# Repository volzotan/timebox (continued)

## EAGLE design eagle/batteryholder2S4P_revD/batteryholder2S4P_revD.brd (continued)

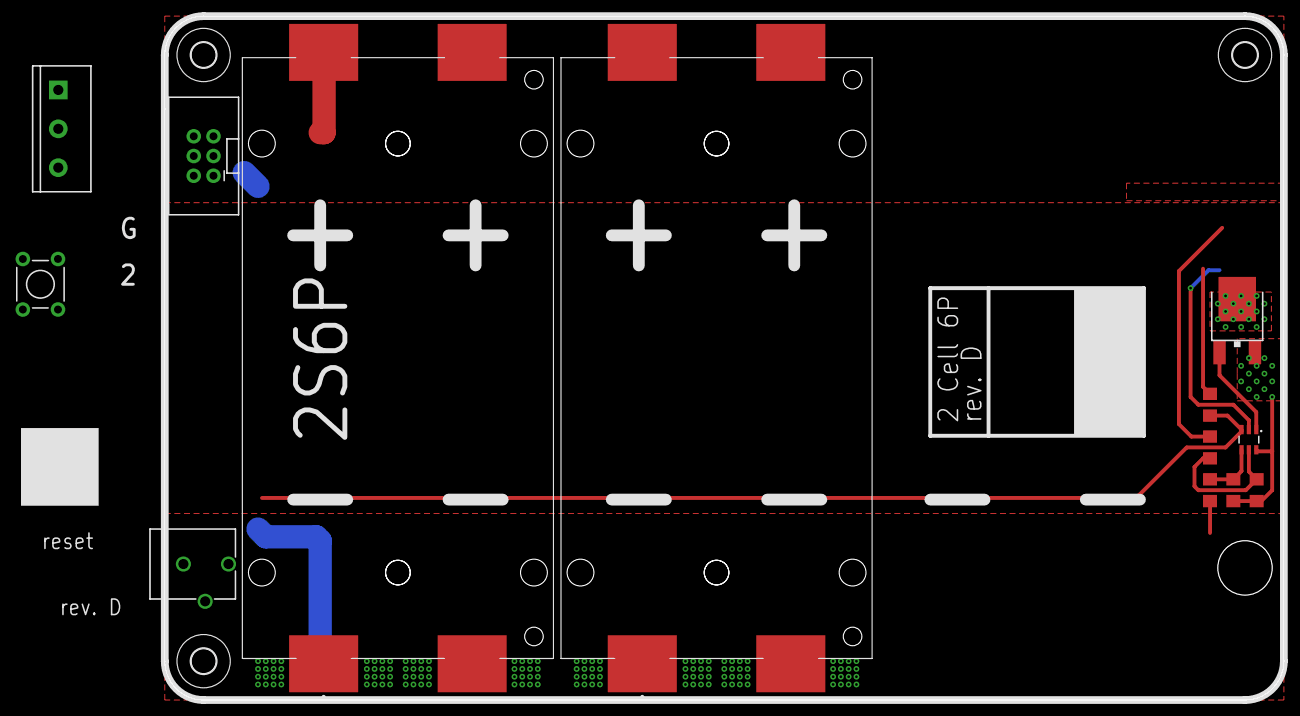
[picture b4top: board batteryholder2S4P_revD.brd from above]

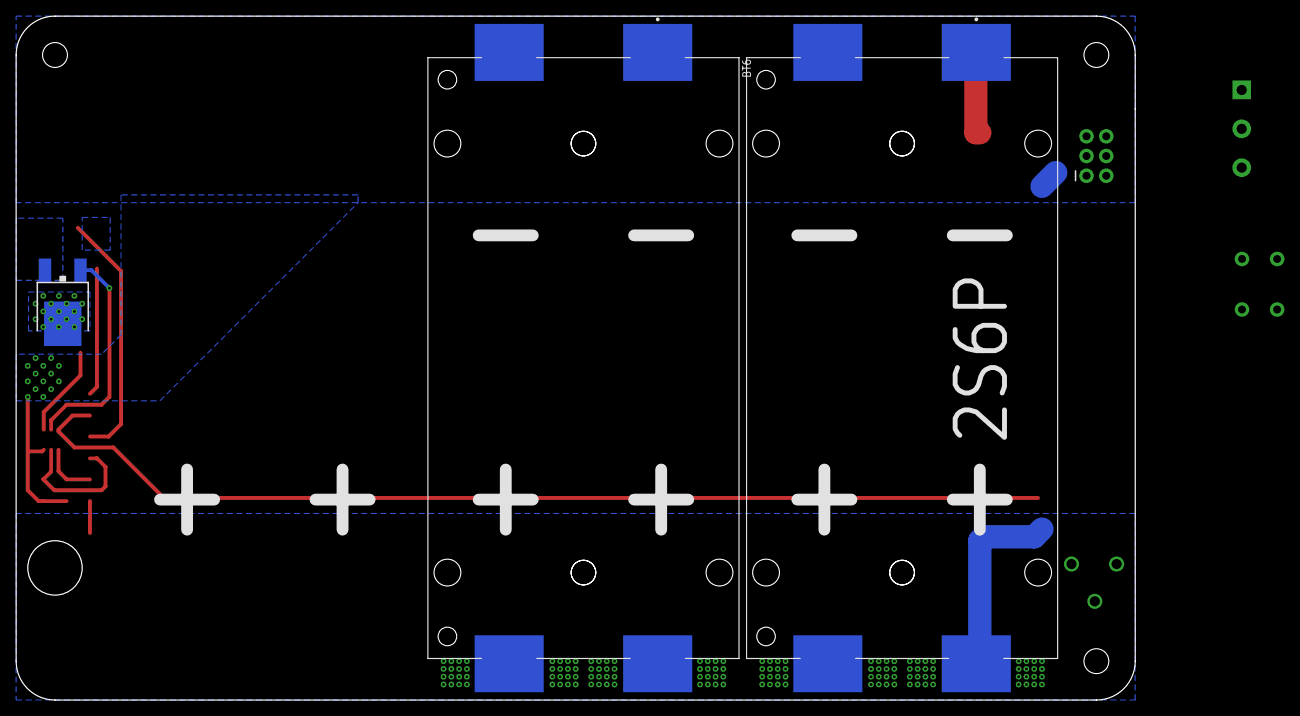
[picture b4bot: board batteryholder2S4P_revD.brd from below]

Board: 2 copper layers, 144.0 x 88.0 mm, 19 parts (3 on the bottom side), 10 nets.

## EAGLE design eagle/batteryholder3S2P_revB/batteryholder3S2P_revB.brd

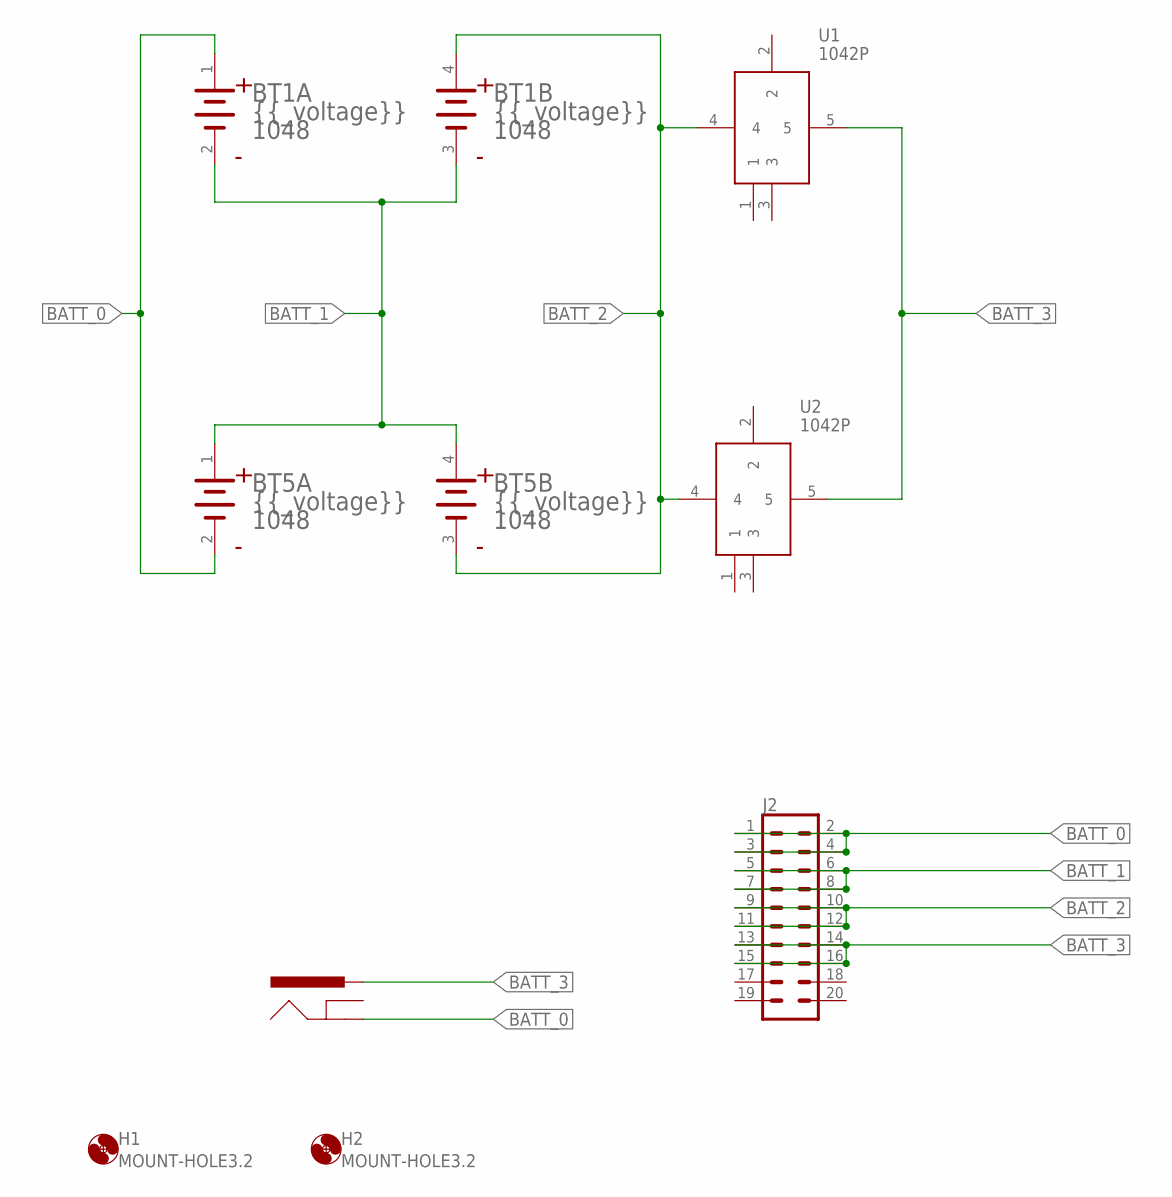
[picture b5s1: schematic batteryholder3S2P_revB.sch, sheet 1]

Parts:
BT1, BT5: KEYSTONE_1048KEYSTONE_1048_0_0; KEYSTONE_1048_0
H1, H2: MOUNT-HOLE3.2; 3,2
J2: CONN_10X2NOSILK; 2X10_NOSILK
J3: POWER_JACKPTH_BREAD; POWER_JACK_PTH_BREAD
U1, U2: 1042P

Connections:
BATT_0: BT1.1 (1_ANODE), BT5.2 (1_CATHODE), J2.1, J2.2, J2.3, J2.4, J3.GND
BATT_1: BT1.2 (1_CATHODE), BT1.3 (2_CATHODE), BT5.1 (1_ANODE), BT5.4 (2_ANODE), J2.5, J2.6, J2.7, J2.8
BATT_2: BT1.4 (2_ANODE), BT5.3 (2_CATHODE), J2.9, J2.10, J2.11, J2.12, U1.4, U2.4
BATT_3: J2.13, J2.14, J2.15, J2.16, J3.PWR, U1.5, U2.5

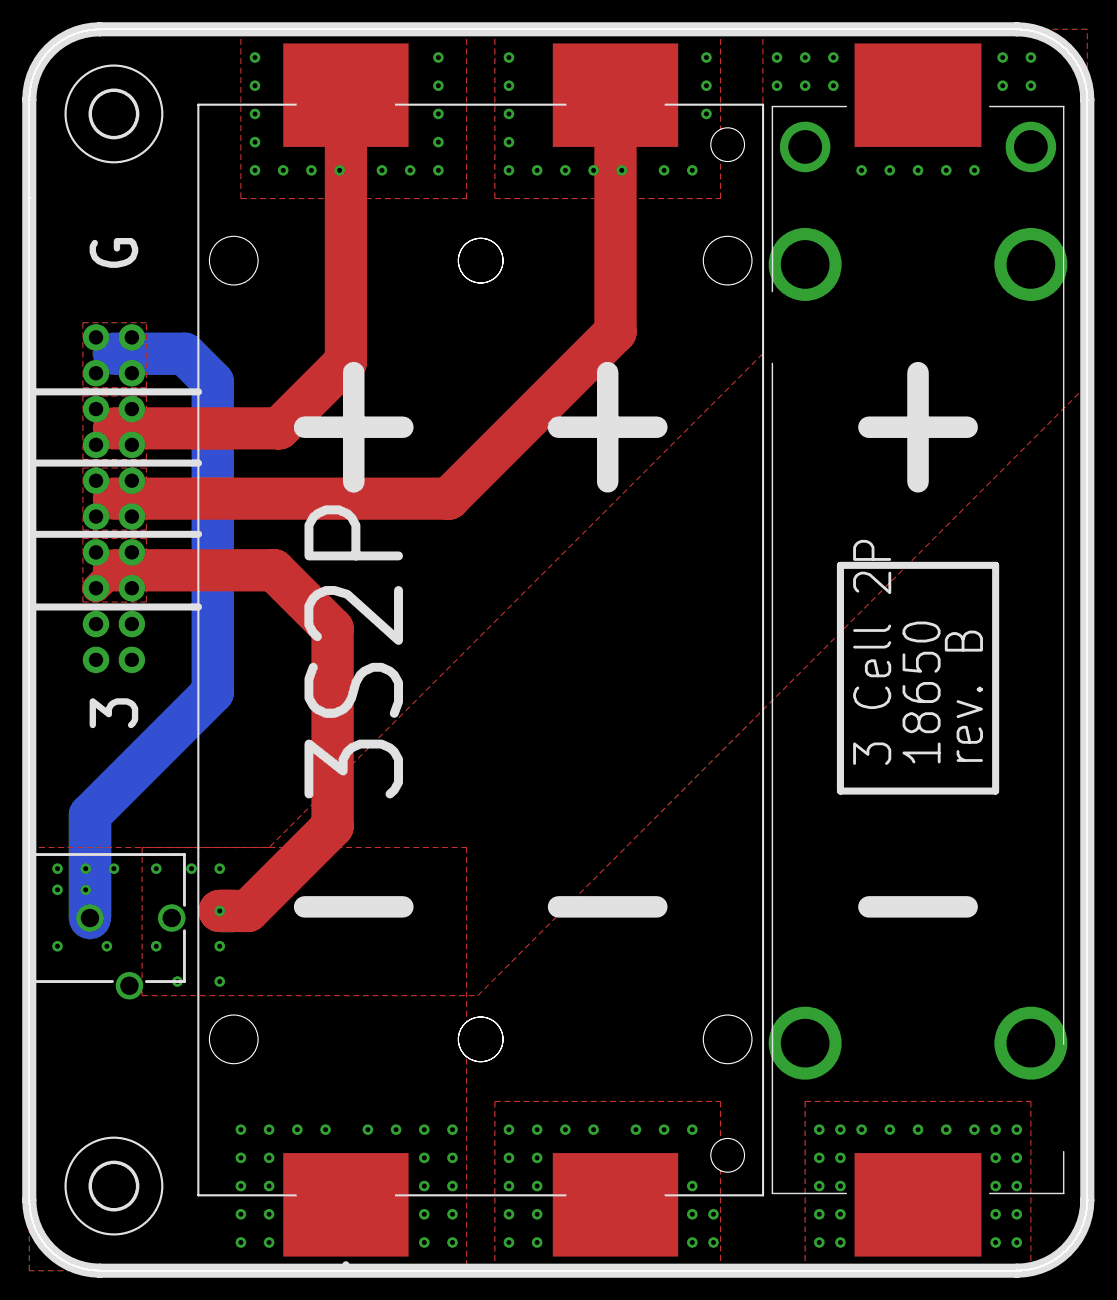
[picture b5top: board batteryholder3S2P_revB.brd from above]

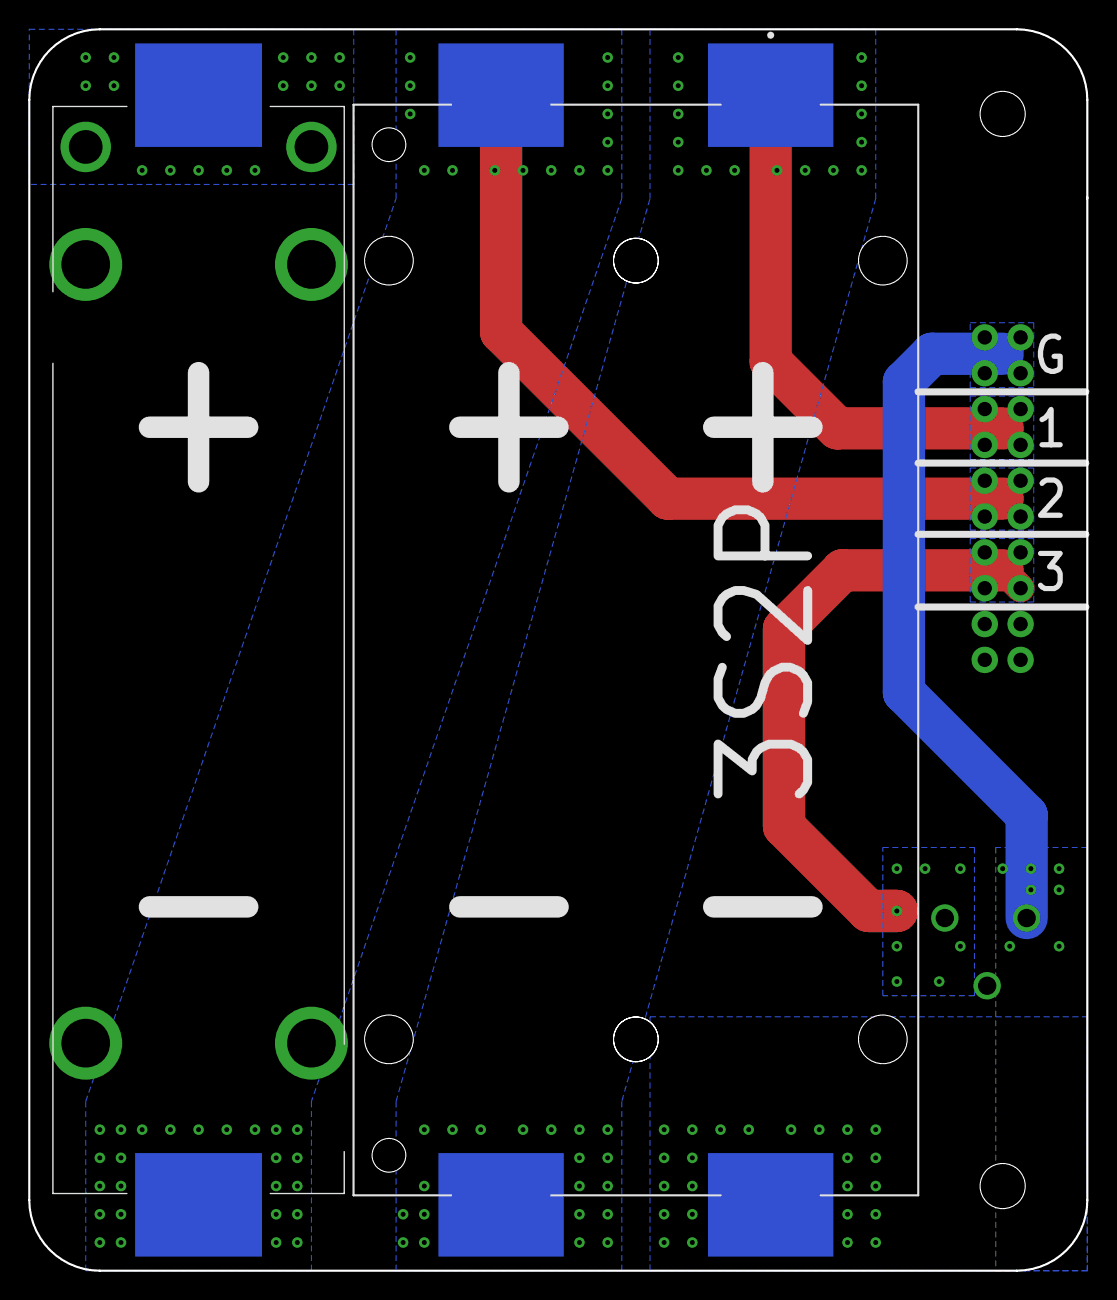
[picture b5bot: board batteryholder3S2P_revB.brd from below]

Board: 2 copper layers, 75.0 x 88.0 mm, 8 parts (2 on the bottom side), 4 nets.

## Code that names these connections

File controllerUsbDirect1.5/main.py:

import sys
import time
import supervisor

import board
from digitalio import DigitalInOut, Direction, Pull
from pulseio import PWMOut

import busio
import adafruit_mcp9808

import neopixel

PIN_BUTTON      = board.D11 # PA16
PIN_USB_EN      = board.D7  # PA21
PIN_LED         = board.D13 # PA17 
PIN_DLOAD       = board.D10 # PA18

# see for pinout:
# https://circuitpython.readthedocs.io/en/3.x/ports/atmel-samd/README.html#pinout

RED = (255, 0, 0)
YELLOW = (255, 150, 0)
GREEN = (0, 255, 0)
BLUE = (0, 0, 255)
WHITE = (255, 255, 255)
CLEAR = (0, 0, 0)


class UsbController(object):

    TIMER_DLOAD_INT = 1.000
    TIMER_DLOAD_DUR = 0.010

    input_buffer = ""

    # timer
    timer_dload = None #time.monotonic() # dummy load on by default # None

    # i2c = busio.I2C(board.SCL, board.SDA)
    # ina219 = adafruit_ina219.INA219(i2c)

    # current consumption ring buffer 
    # ina_current_time = [None] * 100
    # ina_current_value = [None] * 100
    # ina_current_index = 0

    i2c = busio.I2C(board.SCL, board.SDA)
    temp_sensor = adafruit_mcp9808.MCP9808(i2c)

    pixel = neopixel.NeoPixel(PIN_LED, 1, auto_write=True) # , brightness=0.1)

    button = DigitalInOut(PIN_BUTTON)
    button.direction = Direction.INPUT
    button.pull = Pull.UP

    mosfet = DigitalInOut(PIN_USB_EN)
    mosfet.direction = Direction.OUTPUT
    mosfet.value = False

    dummy_load = DigitalInOut(PIN_DLOAD)
    dummy_load.direction = Direction.OUTPUT
    dummy_load_pixel = False
    dummy_load_paused = None

    def __init__(self):     

        # print("INIT")

        # LED status
        self.pixel.fill(GREEN)
        self.pixel.show()
        time.sleep(1.0)
        self.pixel.fill(CLEAR)


    def event(self):

        now = time.monotonic()

        if self.timer_dload is not None and now - self.timer_dload > 0:
            if self.dummy_load.value:
                # print("< {}".format(now - self.timer_dload))
                if self.dummy_load_pixel:
                    self.pixel.fill(CLEAR)
                    self.pixel.show()
                else:
                    self.dummy_load.value = False

                self.timer_dload = self.timer_dload - self.TIMER_DLOAD_DUR + self.TIMER_DLOAD_INT
            else:

                if not self.mosfet.value:
                    # print(">")
                    if self.dummy_load_pixel:
                        self.pixel.fill(WHITE)
                        self.pixel.show()
                    else:
                        self.dummy_load.value = True
                    self.timer_dload = self.timer_dload + self.TIMER_DLOAD_DUR
                    if now - self.timer_dload > 0:
                        self.timer_dload = now + self.TIMER_DLOAD_DUR


    def read_current(self):

        last_index = self.ina_current_index-1%100
        now = time.monotonic()

        if self.ina_current_time[last_index] is not None:
            if now - self.ina_current_time[last_index] < 0.500:
                return
        
        self.ina_current_time[self.ina_current_index] = now
        self.ina_current_value[self.ina_current_index] = self.ina219.current
        self.ina_current_index = (self.ina_current_index + 1) % 100
                           

    def communicate(self):

        if supervisor.runtime.serial_bytes_available:
            c = sys.stdin.read(1)

            if c != "\n":
                self.input_buffer += c

                if len(self.input_buffer) > 100:
                    self.input_buffer = ""
                    print("E buffer length exceeded")
            else:

                if self.input_buffer == "knock":
                    print("K")

                elif self.input_buffer == "on":
                    self.mosfet.value = True
                    time.sleep(0.1)
                    self.pixel.fill(WHITE)
                    self.pixel.show()
                    print("K")

                elif self.input_buffer == "off":
                    self.mosfet.value = False
                    self.pixel.fill(CLEAR)
                    self.pixel.show()
                    print("K")

                elif self.input_buffer == "dummyload on":
                    self.timer_dload = time.monotonic()
                    print("K")

                elif self.input_buffer == "dummyload off":
                    self.timer_dload = None
                    self.dummy_load.value = False
                    print("K")

                elif self.input_buffer == "led on":
                    self.pixel.fill(YELLOW)
                    self.pixel.show()
                    print("K")

                elif self.input_buffer == "led off":
                    self.pixel.fill(CLEAR)
                    self.pixel.show()
                    print("K")

                elif self.input_buffer == "temp":
                    print("K ", sep="")
                    print(self.temp_sensor.temperature)

                elif self.input_buffer == "status":
                    print("K null")

                # elif self.input_buffer == "status v":
                #     print("K ", sep="")
                #     print(self.ina_current_value)

                else:
                    print("E unknown command")

                self.input_buffer = ""


    def loop(self):

        while True:
            self.communicate()
            self.event()
            # self.read_current()
            time.sleep(0.010)


if __name__ == "__main__":

    c = UsbController()
    c.loop()

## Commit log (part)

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2016-08-26 controller2: EXT circuit
2016-08-27 remove lock files
2016-08-27 controller2: 3.5mm headphone jack
2016-08-28 controller2: eagle layout nearly finished
2016-08-28 controller2: net classes for power supply lines
2016-08-28 controller2: silkscreen
2016-08-28 controller2: last silkscreen changes
2016-08-29 controller2: a little bit more padding for the buck converter
2016-08-29 controller2: errors fixed for display connector, power jacks and mosfets
2016-09-15 controller2: firmware (pins set for new hardware)
2016-09-16 controller3 created
2016-09-19 controller2: new display, removed poti code
2016-09-19 controller3: eagle files update
2016-09-24 controller2.5: smaller board
2016-09-24 controller2: major changes for controller2 board
2016-09-27 controller2.5: production version
2016-09-27 controller 2.4 / 3.0 changes
2016-10-02 controller2: sleep option
2016-10-06 eagle: remove bulk files
2016-10-12 controller3: changed board layout for milling
2016-10-16 eagle files
2016-10-25 controller2.5: firmware
2016-10-26 bulk commit (eagle files, old changes)
2016-11-12 controller4 added
2016-11-12 small changes in CAD files
2016-11-13 controller4: added switch (battery -> USB)
2016-11-13 controller4: changed layout
2016-11-14 controller4: moved display to the upper half
2016-11-18 1050: CAD camera measurement values improved.
2016-11-20 1050 CAD: reduced size by 1 mm on width and height to improve pelicase fit
2016-11-24 1050 CAD: smaller base than outer edges to fit pelicase
2016-11-24 controller4: eagle files nearly finished
2016-11-25 controller4: temp sensor and silkscreen
2016-11-26 controller4: final
2016-11-30 1050V2
2016-11-30 1050V2: changes (4mm smaller in height, 2mm smaller in width)
2016-12-01 1050 milled enclosure
2016-12-01 minor changes
2016-12-13 1050V2: batter holder holes removed
2017-01-03 created controller 5
2017-01-05 controller 4 copied
2017-01-07 controller4x
2017-01-10 controller5
2017-01-10 controller5 & controller5Teensy
2017-01-18 1050V2: pressure noses shortened
2017-01-18 controllerHolder
2017-01-23 updating various small files
2017-01-23 1050V3
2017-01-23 gitignore updated for eagle files
2017-01-23 controller6
2017-01-25 controller6: multiport connector
2017-01-26 controller6: minor layout changes
2017-01-28 1050V3: clamp
2017-01-29 1050V3: minor changes
2017-01-29 1050V3: first prototype changes
2017-01-30 1050V3: clamp improvements
2017-01-31 controller6: minor changes
2017-02-06 controller7: routing power board created display board
2017-02-08 controller7: power board finished
2017-02-09 controller7: controllerboard finished
2017-02-11 koekelberg: nut cavities
2017-02-14 zerobox script created
2017-02-15 Ombox removed
2017-02-15 koekelberg: more organic housing shape
2017-02-16 zerobox: platform check
2017-03-02 zerobox: cleanup and changing working directory
2017-03-02 various changes
2017-03-03 controller7: values for voltage divider resistors
2017-03-03 various old changes
2017-03-13 controller 2.5 case top
2017-03-24 1050V3: pressure noses
2017-03-27 1050V4
2017-04-01 1050V4: corner width fixed
2017-05-11 controller10
2017-05-15 socketplate (no captive nuts anymore) 1050V4 (higher tolerances for off center socketplate holes)
2017-05-17 housing refined
2017-05-18 controller10 ready for fab
2017-05-18 controller 10: PCB art
2017-05-28 enclosures
2017-06-02 enclosure files
2017-06-04 clamptest integrated notch
2017-06-12 enclosure and clamptest
2017-06-13 caterina bootloader for Arduino Leonardo
2017-06-13 Caterina Bootloader modified to remove RX/TX LEDs
2017-06-13 Caterina Bootloader setup guide
2017-06-15 changes to the printed housing
2017-06-18 controller10: command parsing progress
2017-06-18 stalho: ready for first print
2017-06-27 stahlo: changes tolerances batteryclip: now working controller10: EEPROM code
2017-06-28 stalho1 and 2
2017-06-30 controller10: minor bugfixes
2017-07-02 clamp 1050: slightly increased height
2017-07-06 controller10: proper debug statements
2017-07-06 controller10: additional zero configuration values
2017-07-13 controller10: settle on an configuration package for zero, not single variables
2017-07-13 controller10: bugfix (overflow in zero sleep calculation)
2017-07-18 zeroholder: easier access to sd card
2017-07-19 zeroholder: circle cutouts for button
2017-07-27 removed old box code
2017-08-08 controller11: new board layout
2017-08-20 enclosure #3 created
2017-08-24 controller11: nano fit
2017-09-19 controller11: progress in routing
2017-09-22 controller11: routed all airwires
2017-09-23 controller11: fixed silkscreen
2017-09-26 zeroholder11 created
2017-10-01 zeroholder11: top changed
2017-12-27 controller 10 firmware duplicated
2017-12-27 enclosure for Pelicase 1120
2017-12-28 controller11: pinout and LED timer
2017-12-28 controller12: marked unusable pins (bootloader RX/TXLED on 32U4)
2017-12-28 old changes to various scad files
2017-12-31 controller12: added header for possible extension board
2018-01-05 rename
2018-01-05 removed old summaerybox files created empty install manual for zerobox
2018-01-10 controller11: bugfix
2018-01-13 zeroholder11: finished enclosure with pi
2018-02-03 controller 12 progress zero_standalone enclosure
2018-02-03 zeroholder11 cleaned up
2018-02-08 zero standalone: non round corners for easier gasket cutting
2018-02-14 controller12: LCD board created
2018-02-15 zeroholder11: cleanup
2018-02-15 1120: added holder for the zeroholder
2018-02-16 bugfix
2018-02-20 zero_standalone: seal 1mm moved camholder to avoid screw collision with pi hdmi port
2018-02-21 zeroholder11: bugfixes
2018-02-23 zero_standalone: added cutout for rubber seal
2018-02-23 added different sizes for center drill
2018-03-02 zero standlone: tolerances tighter for seal cutting helper
2018-04-17 enclosure 1020: bottom/top sizes adjusted
2018-10-04 1120: from round corners to octagonal adjusted some sizes
2018-10-06 1120: extension holes in back part
2018-10-12 1120: CNC front part
2018-10-27 1120: slightly smaller sized holes for tighter tolerances
2019-01-17 controller14: progress
2019-01-20 controller14: nearly done
2019-01-21 controller14: finished
2019-01-29 zerobox: test script for direct libgphoto2 usage with python-gphoto2 wrappers
2019-01-31 PTP: autofocus
2019-02-03 zerobox: display tests
2019-03-03 controller14 code
2019-03-03 eagle files usbDirectController
2019-03-06 zerobox oled display progress
2019-03-07 zerobox menu for display progress
2019-03-08 zerobox: refactoring and systemd service
2019-03-08 zerobox: rpyc tests
2019-03-09 zerobox: status
2019-03-09 zerobox: double exposure
2019-03-13 updated gitignore and minimum size oled fonts
2019-03-13 circuitpython program for usbDirectController
2019-03-16 zerobox: DS3231 support
2019-03-21 zerobox: major changes
2019-03-25 zerobox: free space and usbDirectController communication
2019-03-27 zerobox: free disk progress bars
2019-03-27 bugfix camera detecting
2019-04-01 bugfixes
2019-04-02 gitignore and minor changes
2019-04-07 multiprocessing.pool used for triggering minor changes and bugfixes
2019-04-16 zerobox gui: loading and saving of config files
2019-04-24 zerobox gui: refactoring from script to class adding delay option to the scheduler
2019-04-25 zeroboxConnector standalone
2019-04-27 zerobox: updated install and upload scripts bugfixes
2019-04-28 client_test and bugfixes
2019-05-02 usbDirectController2
2019-05-04 refactoring and UsbHubController
2019-05-20 minor changes usbDirectController
2019-05-20 zerobox: now shows number of errors during session
2019-05-27 usbDirectController sent to fab
2019-07-02 zerobox refactoring and changes
2019-07-06 usbDirectController1.5 firmware
2019-07-06 controller11_2 board schematics created
2019-07-06 zerobox: adding support for controller11
2019-07-06 samd21 arduino zero bootloader
2019-07-11 zerobox: device detection (ping command)
2019-07-11 zerobox: battery readings from controller11 ykushxs device support
2019-07-21 zerobox: bugfixes and cleanup
2019-07-21 zerobox: CLI script
2019-07-23 zerobox CLI enhancements
2019-07-25 bugfixes and screensaver
2019-07-25 bugfixes config position selecting
2019-07-26 zerobox log used memory disable constant camera detecting
2019-07-26 TimeboxApp via OpenMemories
2019-07-28 bugfixes CLI connector
2019-07-28 bugfixes and minor changes
2019-07-31 webConnector for servpat, bugfixes
2019-08-02 zerobox: low voltage shutdown, camera battery reading, bugfixes
2019-08-02 buildroot: added packages
2019-08-05 moved buildroot files
2019-08-07 zerobox: primary and secondary image directories, bugfixes
2019-08-08 zerobox async get_status
2019-08-24 controller11_standalone with +/-3EV mode
2019-08-25 controller11_standalone: shorter trigger duration ELF files added to gitignore
2019-08-28 UDC3 bugfixes
2019-08-28 UDC3: temperature sensor
2019-09-14 eagle batteryholder 2P8S board
2019-09-14 updated gitignore
2019-09-30 new PCB files (batteryholder, templog2, ...)
2019-09-30 batteryholder 2S6P added polarity signs on silkscreen
2019-10-07 UDC3 and controller15 firmwares
2019-10-07 batteryholder boards minor changes
2019-10-19 zerobox: UsbDirectController (UDC2 and 3) and SerialController (controller11) removed. TimeboxController (controller15) added...
2019-10-21 bugfixes (Lock for TimeboxController device)
2019-10-28 eagle: 2S6P batteryhold rev. C (with protection IC), controller15_3 and etc.
2019-10-29 cleanup commit (various changes)
2019-10-29 buildroot files
2019-11-04 zerobox: wifi off on session start
2019-11-04 eagle: BMS breakout 2
2019-11-24 buildroot: use external tree
2019-11-25 zerobox: install scripts
2019-11-26 gobject removed from buildroot
2019-12-01 oneshot.py
2019-12-31 oneshot and buildroot update
2019-12-31 controller15 update for oneshot mode
2020-01-05 buildroot gphoto2 package changed description text
2020-01-15 batteryholder revisions and controller17
2020-02-11 created trashcam
2020-02-11 buildroot: additional python packages
2020-02-11 trashcam: minor changes
2020-02-11 eagle files for zerocam boards
2020-02-15 trashcam controller and script
2020-02-15 C preprocessor statement bugfixes
2020-02-19 trashcam: naming scheme, min free space, spot metering, ...
2020-02-21 trashcam: exposure 3 and bugfixes
2020-02-23 trashcam: set time on pi zero and raw bayer data
2020-02-26 trashcam: bugfix, gain too high for second and third exposure
2020-02-28 trashcam: capture 3 five stops higher than cap2
2020-03-02 buildroot: increase wait times for resizing partition
2020-03-02 trashcam: increase/reduce interval calculation based on image brightness by pillow
2020-03-09 trashcam: reduced brightness values for increase/reduce significantly (otherwise ND10+fisheye is causing problems)
2020-03-14 trashcam: install, upload and clean scripts refined
2020-03-14 trashcam: less sync
2020-03-14 controllerTrashcam: inc/red of interval immediately applied to the next trigger
2020-03-16 bugfixes and improvements
2020-03-16 trashcam: RO main partition
2020-03-17 trashcam bugfixes: RO/RW remounting
2020-03-17 minor changes and cleanups
2020-03-28 zerobox2S1P enclosure
2020-03-31 trashcam: debug registers
2020-03-31 removed buildroot pi2 config
2020-03-31 gitignore updated
2020-04-10 trashcam: zipping and adjusted brightness sensitivity for interval change
2020-04-21 controllerTrashcam: bugfixes and changes for sleepmode
2020-05-06 trashcamController: sleep mode bugfixes
2020-05-30 bugfixes resolution HQ camera MODULO_RAW setting added
2020-06-14 scripts for SAMD21 bootloader flashing
2020-06-14 trashcam: calculating brightness done in background thread (-5s runtime)
2020-06-27 created zerocam rev E PCB
2020-06-29 trashcam: longer capture_1 bugfixes
2021-03-13 eagle: added flexcable
2023-08-21 various uncommitted files
2023-08-21 bootloader flashing script
2023-08-21 mindcontrolhat
2023-08-27 mindcontrolhat: bugfixes + sleeping based on time.monotonic()
2024-09-06 mindcontrolhat: libraries and CAD files
